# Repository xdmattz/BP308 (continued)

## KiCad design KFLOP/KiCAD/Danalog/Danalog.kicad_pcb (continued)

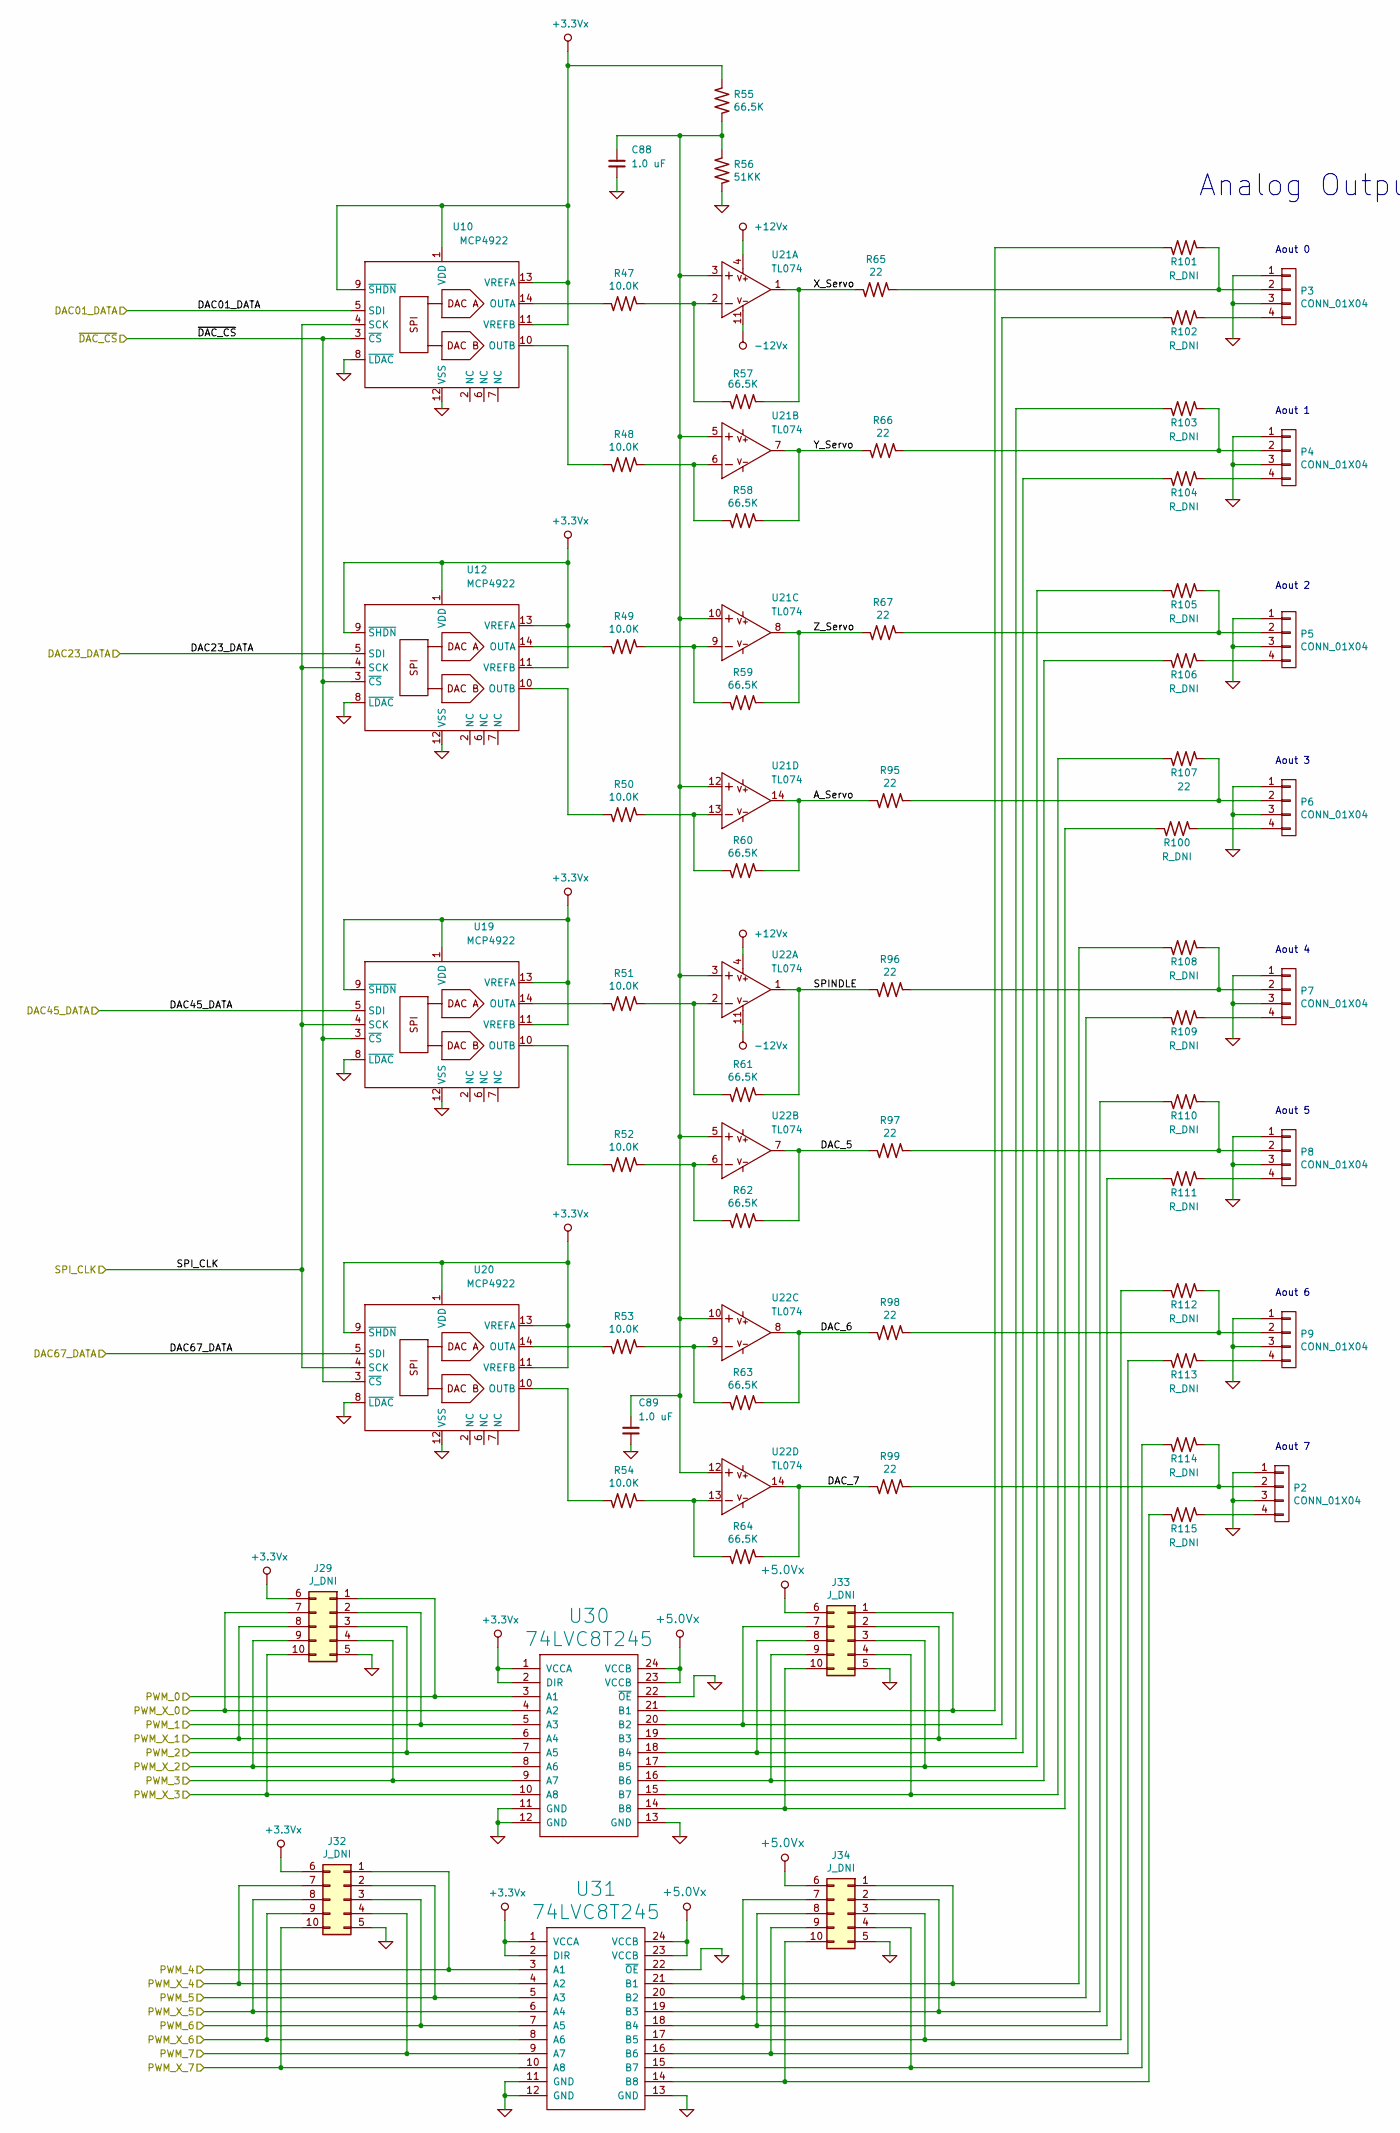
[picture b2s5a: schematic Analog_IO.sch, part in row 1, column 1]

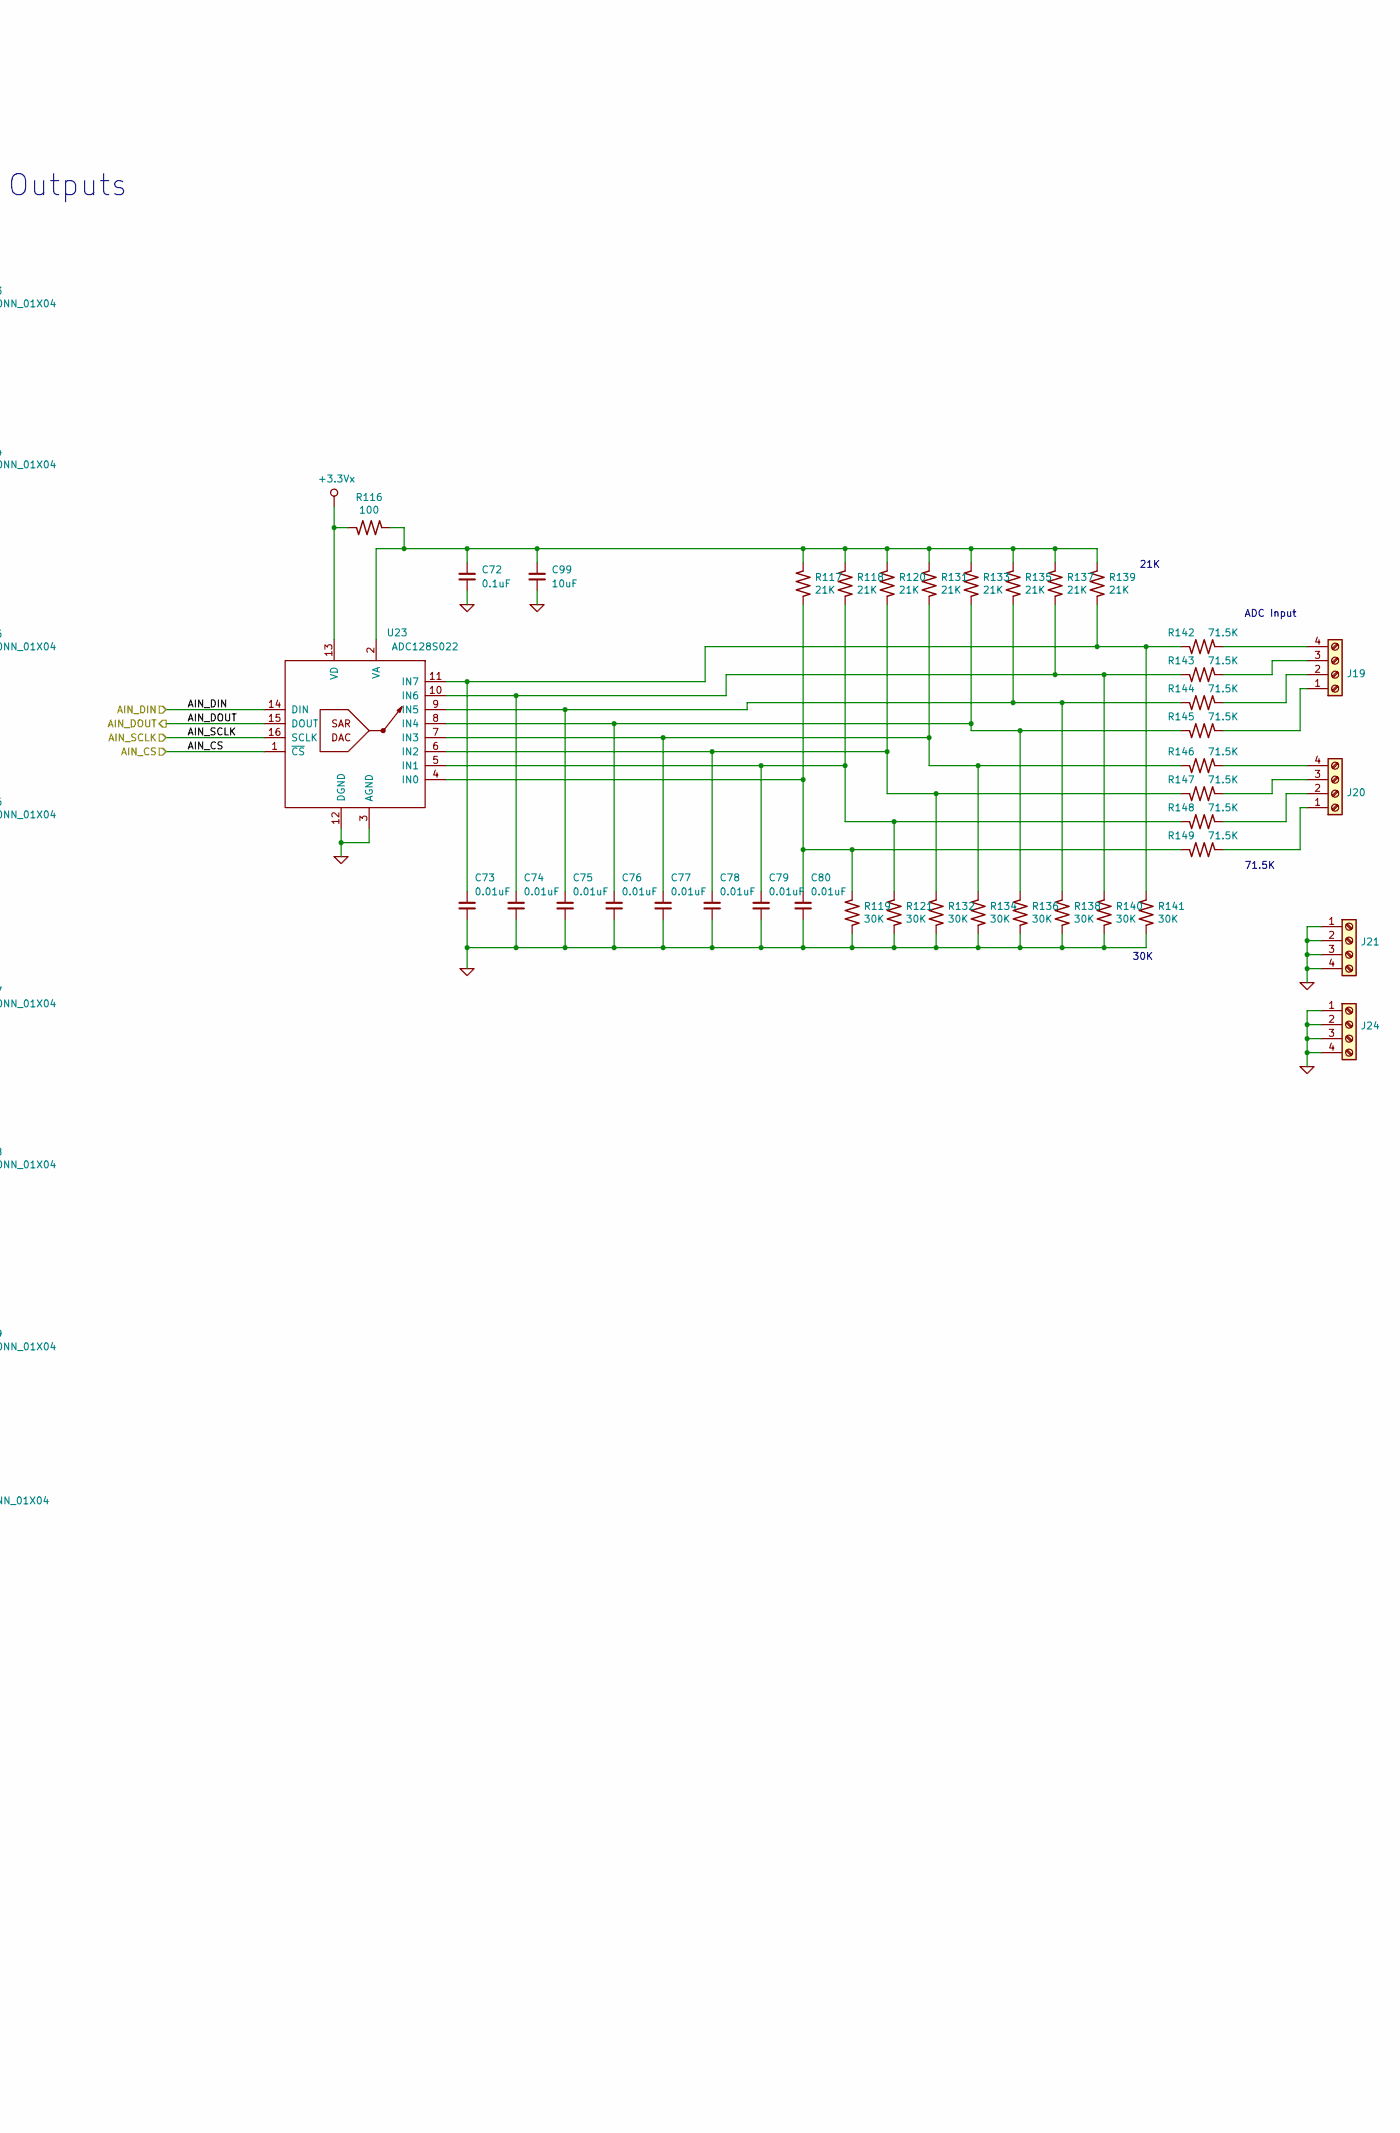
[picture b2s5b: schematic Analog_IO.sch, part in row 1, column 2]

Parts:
C72: 0.1uF; cap_0603
C73, C74, C75, C76, C77, C78, C79, C80: 0.01uF; cap_0603
C88, C89: 1.0 uF; cap_0603
C99: 10uF; cap_0805
J19, J20, J21, J24: Screw_Terminal_01x04; Terminal_Block_RA_4_5_08mm
J29, J32, J33, J34: J_DNI; c-5-103168-3
P2, P3, P4, P5, P6, P7, P8, P9: CONN_01X04; c-5-102202-1
R47, R48, R49, R50, R51, R52, R53, R54: 10.0K; res_0603
R55, R57, R58, R59, R60, R61, R62, R63, R64: 66.5K; res_0603
R56: 51KK; res_0603
R65, R66, R67, R95, R96, R97, R98, R99, R107: 22; res_0603
R100, R101, R102, R103, R104, R105, R106, R108, R109, R110, R111, R112, R113, R114, R115: R_DNI; res_0603
R116: 100; res_0603
R117, R118, R120, R131, R133, R135, R137, R139: 21K; res_0603
R119, R121, R132, R134, R136, R138, R140, R141: 30K; res_0603
R142, R143, R144, R145, R146, R147, R148, R149: 71.5K; res_0603
U10, U12, U19, U20: MCP4922; TSSOP-14_4.4x5mm_Pitch0.65mm
U21, U22: TL074; TSSOP-14_4.4x5mm_Pitch0.65mm
U23: ADC128S022; TSSOP-16
U30, U31: 74LVC8T245; SSOP-24_5.3x8.2mm_Pitch0.65mm

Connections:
+3.3Vx: J29.6, J32.6, R55.2, R116.2, U10.1 (VDD), U10.9 (~SHDN), U10.11 (VREFB), U10.13 (VREFA), U12.1 (VDD), U12.9 (~SHDN), U12.11 (VREFB), U12.13 (VREFA), U19.1 (VDD), U19.9 (~SHDN), U19.11 (VREFB), U19.13 (VREFA), U20.1 (VDD), U20.9 (~SHDN), U20.11 (VREFB), U20.13 (VREFA), U23.13 (VD), U30.1 (VCCA), U30.2 (DIR), U31.1 (VCCA), U31.2 (DIR); also elsewhere on the board
+5.0Vx: J33.6, J34.6, U30.23 (VCCB), U30.24 (VCCB), U31.23 (VCCB), U31.24 (VCCB); also elsewhere on the board
+12Vx: U21.4 (VCC), U22.4 (VCC); also elsewhere on the board
-12Vx: U21.11 (VCC-), U22.11 (VCC-); also elsewhere on the board
/AIN_CS: U23.1 (~CS); also elsewhere on the board
/AIN_DIN: U23.14 (DIN); also elsewhere on the board
/AIN_DOUT: U23.15 (DOUT); also elsewhere on the board
/AIN_SCLK: U23.16 (SCLK); also elsewhere on the board
/Analog/A_Servo: R60.1, R95.2, U21.14 (OUT)
/Analog/DAC_5: R62.1, R97.2, U22.7 (OUT)
/Analog/DAC_6: R63.1, R98.2, U22.8 (OUT)
/Analog/DAC_7: R64.1, R99.2, U22.14 (OUT)
/Analog/SPINDLE: R61.1, R96.2, U22.1 (OUT)
/Analog/X_Servo: R57.1, R65.2, U21.1 (OUT)
/Analog/Y_Servo: R58.1, R66.2, U21.7 (OUT)
/Analog/Z_Servo: R59.1, R67.2, U21.8 (OUT)
/DAC_01: U10.5 (SDI); also elsewhere on the board
/DAC_23: U12.5 (SDI); also elsewhere on the board
/DAC_45: U19.5 (SDI); also elsewhere on the board
/DAC_67: U20.5 (SDI); also elsewhere on the board
/PWM_0: J29.1, U30.3 (A1); also elsewhere on the board
/PWM_1: J29.2, U30.5 (A3); also elsewhere on the board
/PWM_2: J29.3, U30.7 (A5); also elsewhere on the board
/PWM_3: J29.4, U30.9 (A7); also elsewhere on the board
/PWM_4: J32.1, U31.3 (A1); also elsewhere on the board
/PWM_5: J32.2, U31.5 (A3); also elsewhere on the board
/PWM_6: J32.3, U31.7 (A5); also elsewhere on the board
/PWM_7: J32.4, U31.9 (A7); also elsewhere on the board
/PWM_X_0: J29.7, U30.4 (A2); also elsewhere on the board
/PWM_X_1: J29.8, U30.6 (A4); also elsewhere on the board
/PWM_X_2: J29.9, U30.8 (A6); also elsewhere on the board
/PWM_X_3: J29.10, U30.10 (A8); also elsewhere on the board
/PWM_X_4: J32.7, U31.4 (A2); also elsewhere on the board
/PWM_X_5: J32.8, U31.6 (A4); also elsewhere on the board
/PWM_X_6: J32.9, U31.8 (A6); also elsewhere on the board
/PWM_X_7: J32.10, U31.10 (A8); also elsewhere on the board
/SPI_CLK: U10.4 (SCK), U12.4 (SCK), U19.4 (SCK), U20.4 (SCK); also elsewhere on the board
/~DAC_CS: U10.3 (~CS), U12.3 (~CS), U19.3 (~CS), U20.3 (~CS); also elsewhere on the board
GND: C72.2, C73.2, C74.2, C75.2, C76.2, C77.2, C78.2, C79.2, C80.2, C88.2, C89.2, C99.2, J21.1, J21.2, J21.3, J21.4, J24.1, J24.2, J24.3, J24.4, J29.5, J32.5, J33.5, J34.5, P2.1, P2.3, P3.1, P3.3, P4.1, P4.3, P5.1, P5.3, P6.1, P6.3, P7.1, P7.3, P8.1, P8.3, P9.1, P9.3, R56.1, R119.1, R121.1, R132.1, R134.1, R136.1, R138.1, R140.1, R141.1, U10.8 (~LDAC), U10.12 (VSS), U12.8 (~LDAC), U12.12 (VSS), U19.8 (~LDAC), U19.12 (VSS), U20.8 (~LDAC), U20.12 (VSS), U23.3 (AGND), U23.12 (DGND), U30.11 (GND), U30.12 (GND), U30.13 (GND), U30.22 (~OE), U31.11 (GND), U31.12 (GND), U31.13 (GND), U31.22 (~OE); also elsewhere on the board
unnamed: C72.1, C99.1, R116.1, R117.2, R118.2, R120.2, R131.2, R133.2, R135.2, R137.2, R139.2, U23.2 (VA)
unnamed: C73.1, R139.1, R141.2, R142.1, U23.11 (IN7)
unnamed: C74.1, R137.1, R140.2, R143.1, U23.10 (IN6)
unnamed: C75.1, R135.1, R138.2, R144.1, U23.9 (IN5)
unnamed: C76.1, R133.1, R136.2, R145.1, U23.8 (IN4)
unnamed: C77.1, R131.1, R134.2, R146.1, U23.7 (IN3)
unnamed: C78.1, R120.1, R132.2, R147.1, U23.6 (IN2)
unnamed: C79.1, R118.1, R121.2, R148.1, U23.5 (IN1)
unnamed: C80.1, R117.1, R119.2, R149.1, U23.4 (IN0)
unnamed: C88.1, C89.1, R55.1, R56.2, U21.3 (IN+), U21.5 (IN+), U21.10 (IN+), U21.12 (IN+), U22.3 (IN+), U22.5 (IN+), U22.10 (IN+), U22.12 (IN+)
unnamed: J19.1, R145.2
unnamed: J19.2, R144.2
unnamed: J19.3, R143.2
unnamed: J19.4, R142.2
unnamed: J20.1, R149.2
unnamed: J20.2, R148.2
unnamed: J20.3, R147.2
unnamed: J20.4, R146.2
unnamed: J33.1, R101.2, U30.21 (B1)
unnamed: J33.2, R103.2, U30.19 (B3)
unnamed: J33.3, R105.2, U30.17 (B5)
unnamed: J33.4, R107.2, U30.15 (B7)
unnamed: J33.7, R102.2, U30.20 (B2)
unnamed: J33.8, R104.2, U30.18 (B4)
unnamed: J33.9, R106.2, U30.16 (B6)
unnamed: J33.10, R100.2, U30.14 (B8)
unnamed: J34.1, R108.2, U31.21 (B1)
unnamed: J34.2, R110.2, U31.19 (B3)
unnamed: J34.3, R112.2, U31.17 (B5)
unnamed: J34.4, R114.2, U31.15 (B7)
unnamed: J34.7, R109.2, U31.20 (B2)
unnamed: J34.8, R111.2, U31.18 (B4)
unnamed: J34.9, R113.2, U31.16 (B6)
unnamed: J34.10, R115.2, U31.14 (B8)
unnamed: P2.2, R99.1, R114.1
unnamed: P2.4, R115.1
unnamed: P3.2, R65.1, R101.1
unnamed: P3.4, R102.1
unnamed: P4.2, R66.1, R103.1
unnamed: P4.4, R104.1
unnamed: P5.2, R67.1, R105.1
unnamed: P5.4, R106.1
unnamed: P6.2, R95.1, R107.1
unnamed: P6.4, R100.1
unnamed: P7.2, R96.1, R108.1
unnamed: P7.4, R109.1
unnamed: P8.2, R97.1, R110.1
unnamed: P8.4, R111.1
unnamed: P9.2, R98.1, R112.1
unnamed: P9.4, R113.1
unnamed: R47.1, R57.2, U21.2 (IN-)
unnamed: R47.2, U10.14 (OUTA)
unnamed: R48.1, R58.2, U21.6 (IN-)
unnamed: R48.2, U10.10 (OUTB)
unnamed: R49.1, R59.2, U21.9 (IN-)
unnamed: R49.2, U12.14 (OUTA)
unnamed: R50.1, R60.2, U21.13 (IN-)
unnamed: R50.2, U12.10 (OUTB)
unnamed: R51.1, R61.2, U22.2 (IN-)
unnamed: R51.2, U19.14 (OUTA)
unnamed: R52.1, R62.2, U22.6 (IN-)
unnamed: R52.2, U19.10 (OUTB)
unnamed: R53.1, R63.2, U22.9 (IN-)
unnamed: R53.2, U20.14 (OUTA)
unnamed: R54.1, R64.2, U22.13 (IN-)
unnamed: R54.2, U20.10 (OUTB)

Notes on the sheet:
ADC Input
30K
71.5K
21K
Analog Outputs
Aout 0
Aout 1
Aout 2
Aout 3
Aout 4
Aout 5
Aout 6
Aout 7

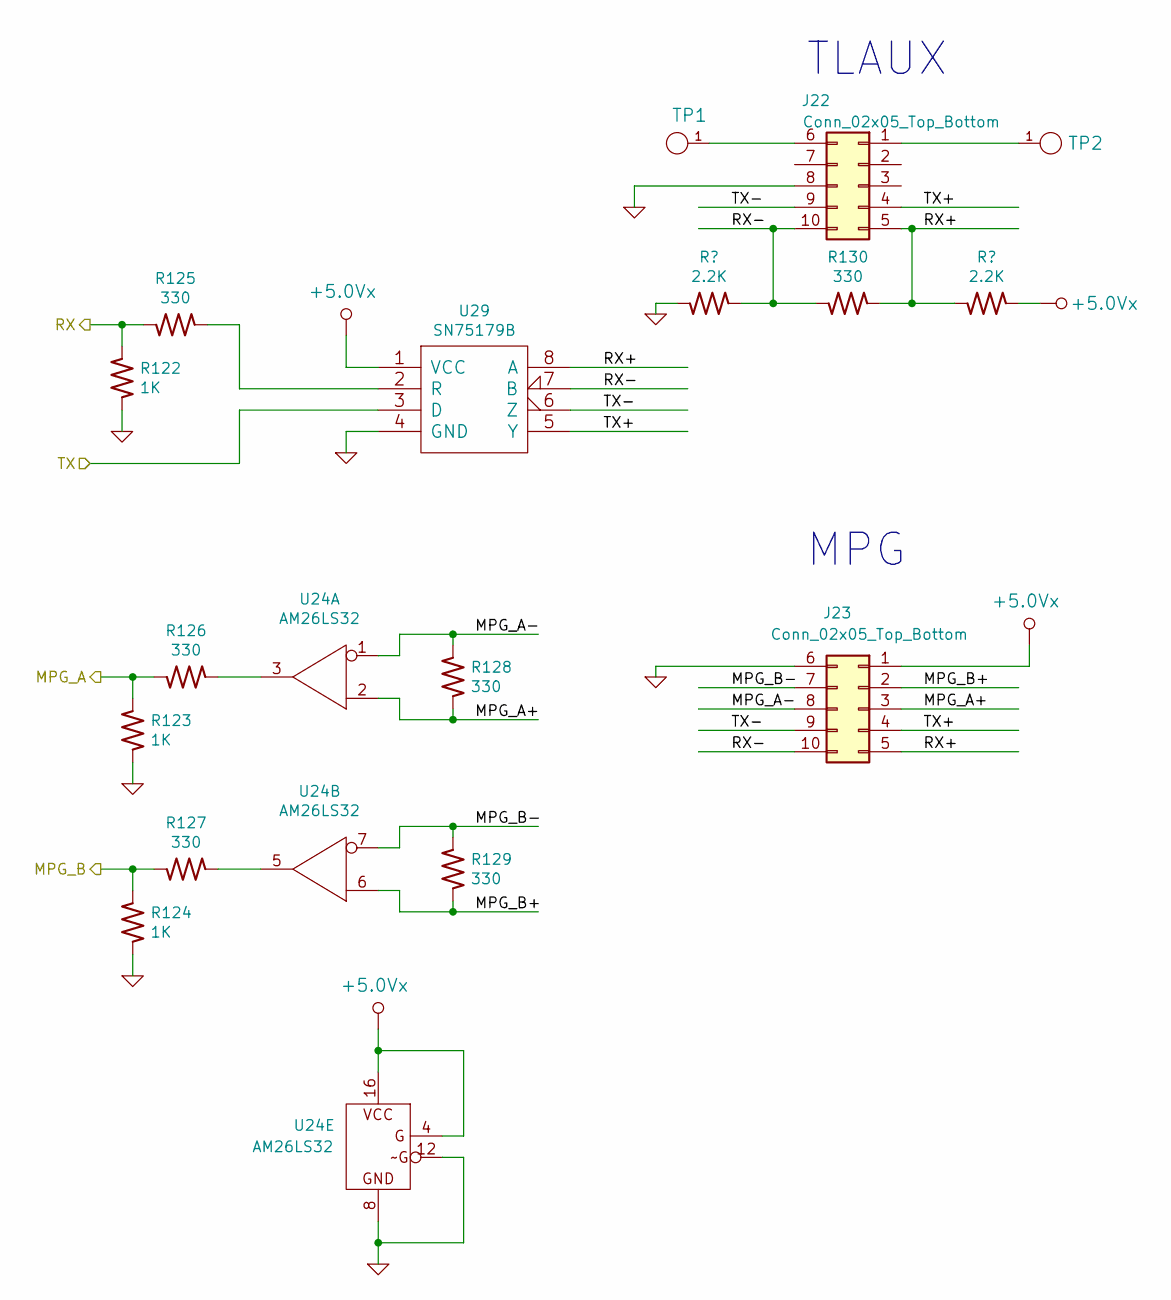
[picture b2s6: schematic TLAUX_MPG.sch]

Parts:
J22, J23: Conn_02x05_Top_Bottom; c-5-103168-3
R122, R123, R124: 1K; res_0603
R125, R126, R127, R128, R129, R130: 330; res_0603
TP1, TP2: TEST_POINT; TP60
U24: AM26LS32; SOIC-16_3.9x9.9mm_Pitch1.27mm
U29: SN75179B; SOIC-8

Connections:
+5.0Vx: J23.1, U24.4 (G), U24.16 (VCC), U29.1 (VCC); also elsewhere on the board
/MPG_A: R123.2, R126.2; also elsewhere on the board
/MPG_B: R124.2, R127.2; also elsewhere on the board
/RS232R_3V: R122.2, R125.2; also elsewhere on the board
/RS232X_3V: U29.3 (D); also elsewhere on the board
/TLAUX_MPG/MPG_A+: J23.3, R128.1, U24.2 (1A)
/TLAUX_MPG/MPG_A-: J23.8, R128.2, U24.1 (1B)
/TLAUX_MPG/MPG_B+: J23.2, R129.1, U24.6 (2A)
/TLAUX_MPG/MPG_B-: J23.7, R129.2, U24.7 (2B)
/TLAUX_MPG/RX+: J22.5, J23.5, R130.1, U29.8 (A)
/TLAUX_MPG/RX-: J22.10, J23.10, R130.2, U29.7 (B)
/TLAUX_MPG/TX+: J22.4, J23.4, U29.5 (Y)
/TLAUX_MPG/TX-: J22.9, J23.9, U29.6 (Z)
GND: J22.8, J23.6, R122.1, R123.1, R124.1, U24.8 (GND), U24.12 (~G), U29.4 (GND); also elsewhere on the board
unnamed: J22.1, TP2.1
unnamed: J22.6, TP1.1
unnamed: R125.1, U29.2 (R)
unnamed: R126.1, U24.3 (1Y)
unnamed: R127.1, U24.5 (2Y)

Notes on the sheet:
MPG
TLAUX

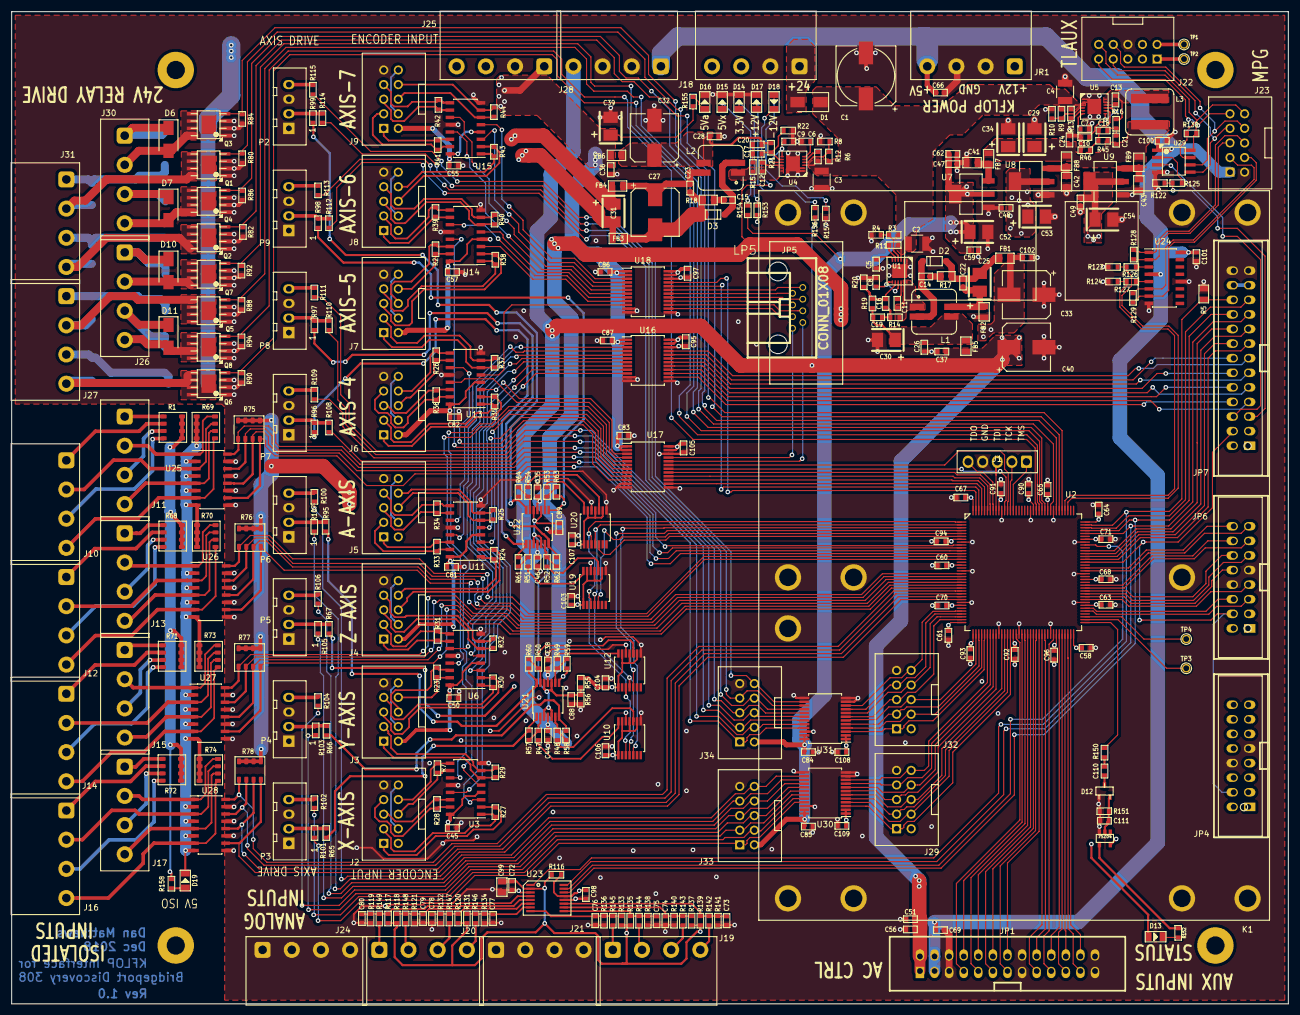
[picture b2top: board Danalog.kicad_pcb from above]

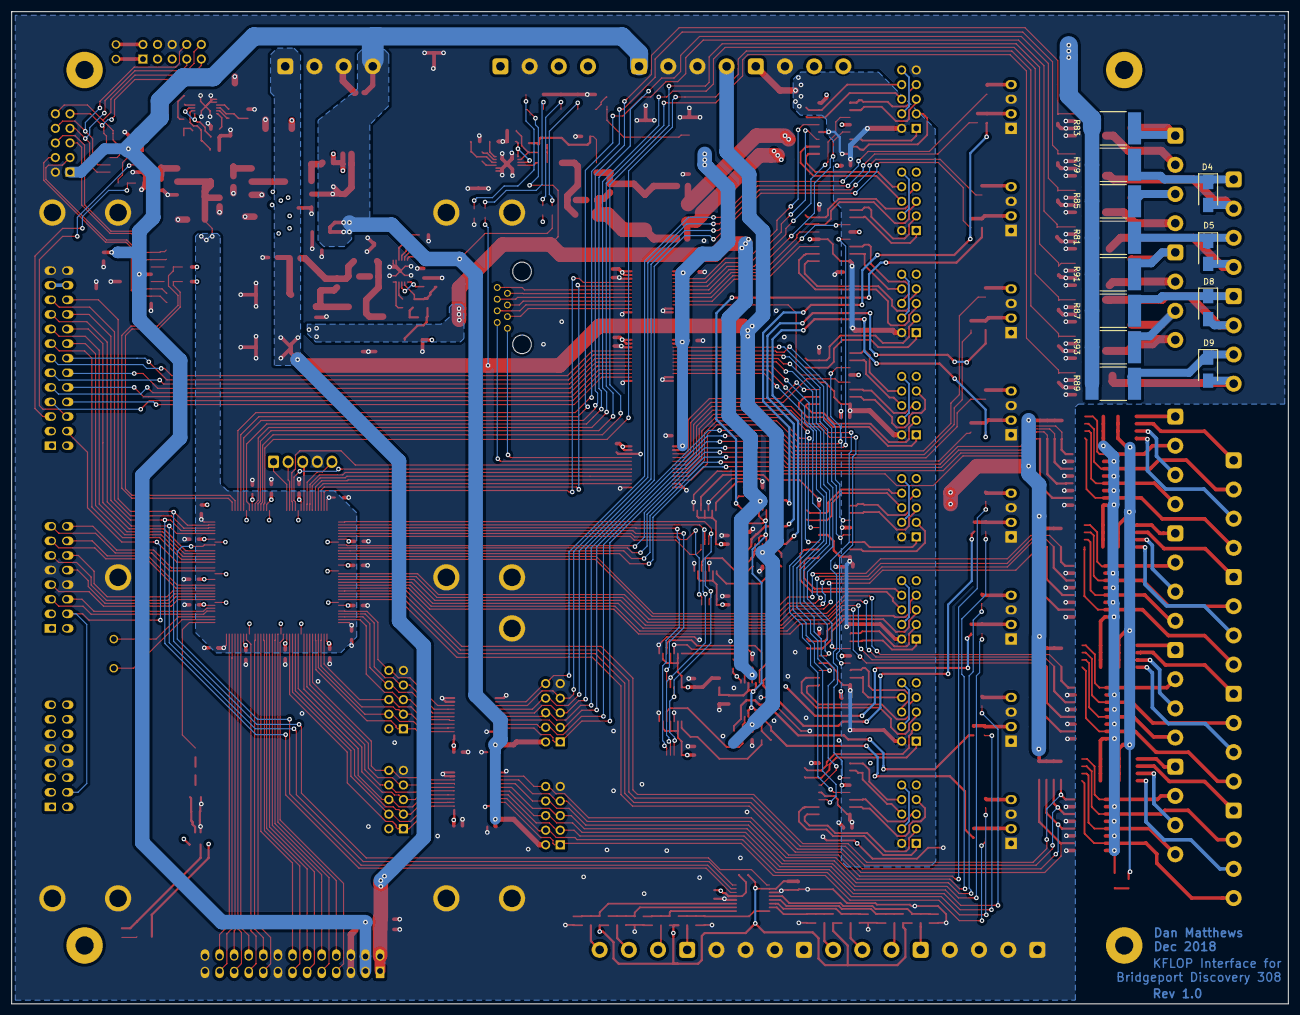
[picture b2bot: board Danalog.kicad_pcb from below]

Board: 4 copper layers, 222.2 x 172.7 mm, 393 parts (12 on the bottom side), 393 nets.

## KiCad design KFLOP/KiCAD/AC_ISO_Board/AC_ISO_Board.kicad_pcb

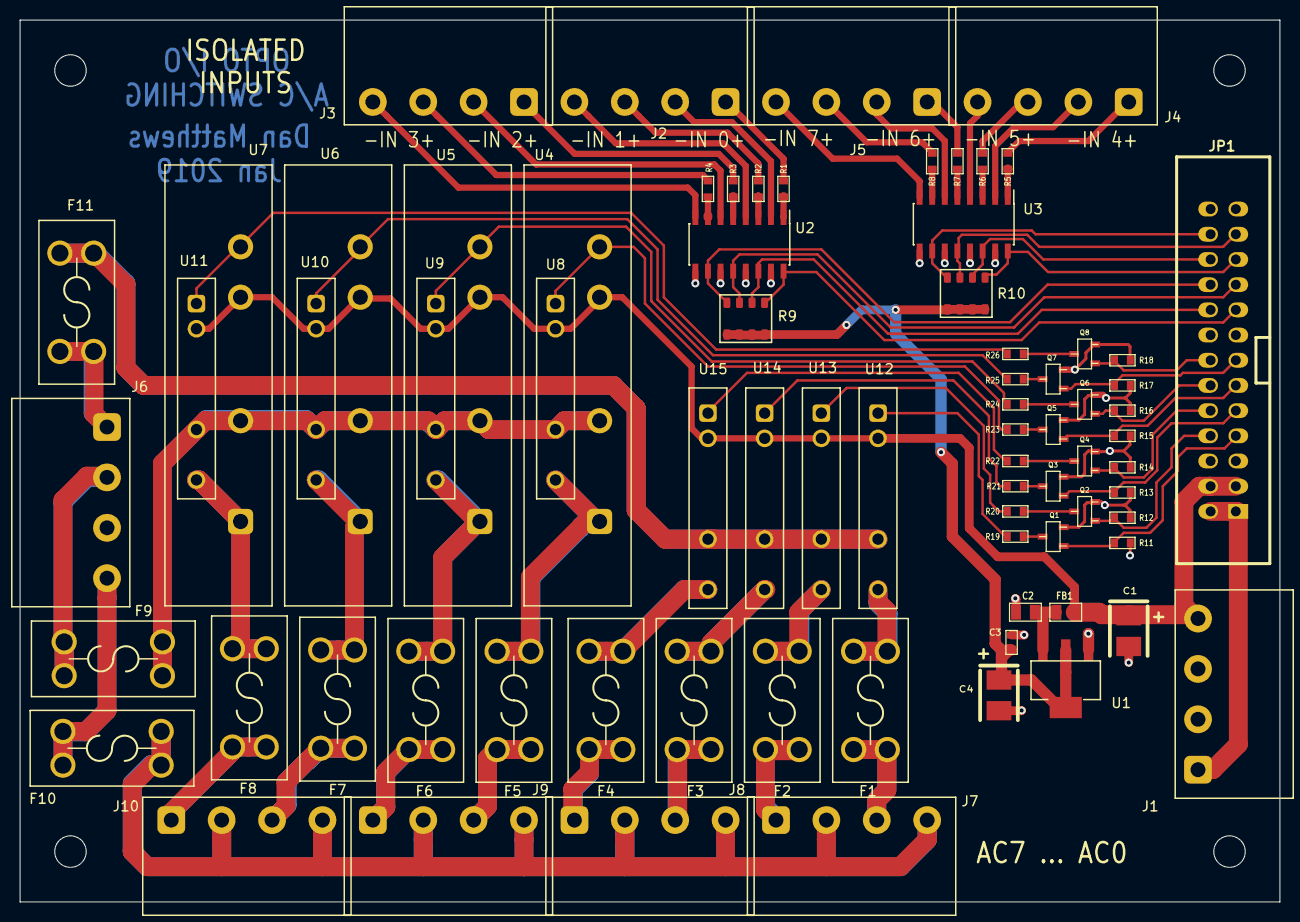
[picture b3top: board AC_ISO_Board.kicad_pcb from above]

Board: 2 copper layers, 127.0 x 88.9 mm, 76 parts (0 on the bottom side), 83 nets.

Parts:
C1, C4: 100uF 6.3V; Tan_Cap_B
C2: 10uF; cap_0805
C3: 0.1uF; cap_0603
F1, F2, F3, F4, F5, F6, F7, F8, F9, F10, F11: Fuse; FUSE_Holder_297
FB1: FB_60 Ohm; fb_0805
J1, J2, J3, J4, J5, J6, J7, J8, J9, J10: Screw_Terminal_01x04; Terminal_Block_RA_4_5_08mm
JP1: CONN_02X13; vasch_strip_13x2
Q1, Q2, Q3, Q4, Q5, Q6, Q7, Q8: BSS-123; sot-23
R1, R2, R3, R4, R5, R6, R7, R8, R19, R20, R21, R22, R23, R24, R25, R26: 2.2K; res_0603
R9, R10: 2.2K; RES_ARRAY_2012
R11, R12, R13, R14, R15, R16, R17, R18: 10K; res_0603
U1: TLV1117LV33; SOT-223
U2, U3: TLP291-4; SOIC-16_3.9x9.9mm_Pitch1.27mm
U4, U5, U6, U7: OACM-UJ
U8, U9, U10, U11, U12, U13, U14, U15: CPC1966; CPC1966Y

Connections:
+3.3Vx: C3.2, C4.1, R9.1, R9.2, R9.3, R9.4, R10.1, R10.2, R10.3, R10.4, U1.2, U1.4
+5.0Vx: C1.1, FB1.2, J1.4, JP1.3, JP1.4, U4.3, U5.3, U6.3, U7.3, U8.2, U9.2, U10.2, U11.2, U12.2, U13.2, U14.2, U15.2
+12Vx: J1.1, JP1.1, JP1.2
/AC_0: JP1.7, Q1.1, R11.2
/AC_1: JP1.8, Q2.1, R12.2
/AC_2: JP1.9, Q3.1, R13.2
/AC_3: JP1.10, Q4.1, R14.2
/AC_4: JP1.11, Q5.1, R15.2
/AC_5: JP1.12, Q6.1, R16.2
/AC_6: JP1.13, Q7.1, R17.2
/AC_7: JP1.14, Q8.1, R18.2
/AUX_IN_0: JP1.17, R9.5, U2.16
/AUX_IN_1: JP1.18, R9.6, U2.14
/AUX_IN_2: JP1.19, R9.7, U2.12
/AUX_IN_3: JP1.20, R9.8, U2.10
/AUX_IN_4: JP1.21, R10.5, U3.16
/AUX_IN_5: JP1.22, R10.6, U3.14
/AUX_IN_6: JP1.23, R10.7, U3.12
/AUX_IN_7: JP1.24, R10.8, U3.10
GND: C1.2, C2.1, C3.1, C4.2, J1.2, J1.3, JP1.5, JP1.6, JP1.15, JP1.16, JP1.25, JP1.26, Q1.2, Q2.2, Q3.2, Q4.2, Q5.2, Q6.2, Q7.2, Q8.2, R11.1, R12.1, R13.1, R14.1, R15.1, R16.1, R17.1, R18.1, U1.1, U2.9, U2.11, U2.13, U2.15, U3.9, U3.11, U3.13, U3.15
unnamed: C2.2, FB1.1, U1.3
unnamed: F1.1, J7.3
unnamed: F1.2, U12.4
unnamed: F2.1, J7.1
unnamed: F2.2, U13.4
unnamed: F3.1, J8.3
unnamed: F3.2, U14.4
unnamed: F4.1, J8.1
unnamed: F4.2, U15.4
unnamed: F5.1, J9.3
unnamed: F5.2, U4.1, U8.4
unnamed: F6.1, J9.1
unnamed: F6.2, U5.1, U9.4
unnamed: F7.1, J10.3
unnamed: F7.2, U6.1, U10.4
unnamed: F8.1, J10.1
unnamed: F8.2, U7.1, U11.4
unnamed: F9.1, J6.2
unnamed: F9.2, U4.2, U5.2, U6.2, U7.2, U8.3, U9.3, U10.3, U11.3
unnamed: F10.1, J6.4
unnamed: F10.2, J7.2, J7.4, J8.2, J8.4, J9.2, J9.4, J10.2, J10.4
unnamed: F11.1, J6.1
unnamed: F11.2, U12.3, U13.3, U14.3, U15.3
unnamed: J2.1, R1.2
unnamed: J2.2, U2.2
unnamed: J2.3, R2.2
unnamed: J2.4, U2.4
unnamed: J3.1, R3.2
unnamed: J3.2, U2.6
unnamed: J3.3, R4.2
unnamed: J3.4, U2.8
unnamed: J4.1, R5.2
unnamed: J4.2, U3.2
unnamed: J4.3, R6.2
unnamed: J4.4, U3.4
unnamed: J5.1, R7.2
unnamed: J5.2, U3.6
unnamed: J5.3, R8.2
unnamed: J5.4, U3.8
unnamed: Q1.3, R19.2
unnamed: Q2.3, R20.2
unnamed: Q3.3, R21.2
unnamed: Q4.3, R22.2
unnamed: Q5.3, R23.2
unnamed: Q6.3, R24.2
unnamed: Q7.3, R25.2
unnamed: Q8.3, R26.2
unnamed: R1.1, U2.1
unnamed: R2.1, U2.3
unnamed: R3.1, U2.5
unnamed: R4.1, U2.7
unnamed: R5.1, U3.1
unnamed: R6.1, U3.3
unnamed: R7.1, U3.5
unnamed: R8.1, U3.7
unnamed: R19.1, U12.1
unnamed: R20.1, U13.1
unnamed: R21.1, U14.1
unnamed: R22.1, U15.1
unnamed: R23.1, U4.4, U8.1
unnamed: R24.1, U5.4, U9.1
unnamed: R25.1, U6.4, U10.1
unnamed: R26.1, U7.4, U11.1

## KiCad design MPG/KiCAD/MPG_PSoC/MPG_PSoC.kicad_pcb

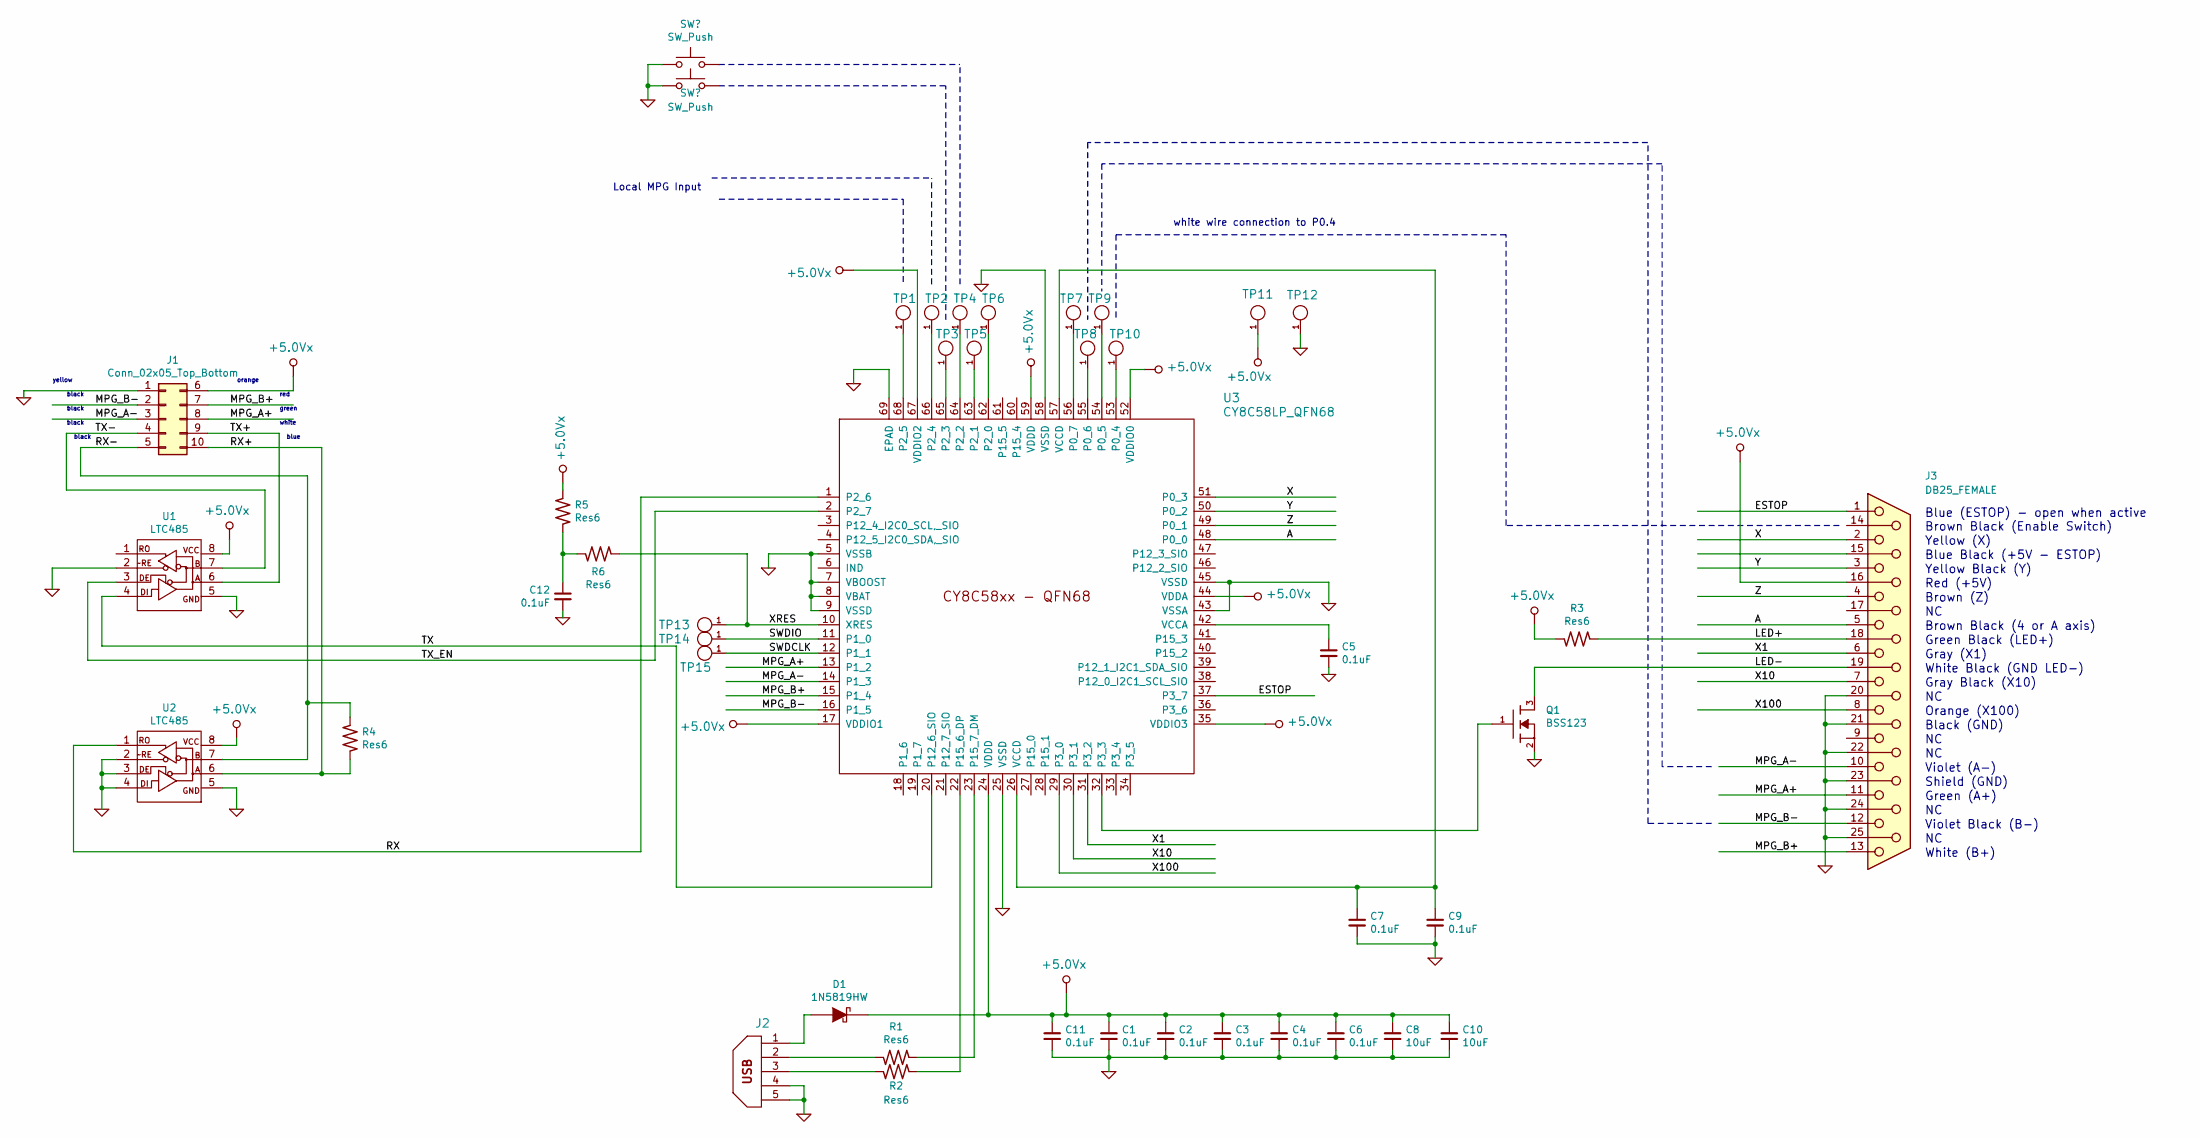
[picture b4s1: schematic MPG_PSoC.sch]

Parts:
C1, C2, C3, C4, C5, C6, C7, C9, C11, C12: 0.1uF; cap_0603
C8, C10: 10uF; cap_1210
D1: 1N5819HW; SOD-123
J1: Conn_02x05_Top_Bottom; c-5-103168-3
J2: USB_micro-B; conn_usb_B_mini_smd
J3: DB25_FEMALE; DB25_F_Edge
Q1: BSS123; sot-23
R1, R2, R3, R4, R5, R6: Res6; res_0603
TP1, TP2, TP3, TP4, TP5, TP6, TP7, TP8, TP9, TP10, TP11, TP12, TP13, TP14, TP15: TP; TP60
U1, U2: LTC485; SOIC-8
U3: CY8C58LP_QFN68; QFN_68

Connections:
+5.0Vx: C1.1, C2.1, C3.1, C4.1, C6.1, C8.1, C10.1, C11.1, D1.2 (K), J1.6, J3.16, R3.2, R5.2, TP11.1, U1.8 (VCC), U2.8 (VCC), U3.17 (VDDIO1), U3.24 (VDDD), U3.35 (VDDIO3), U3.44 (VDDA), U3.52 (VDDIO0), U3.59 (VDDD), U3.67 (VDDIO2)
/A: J3.5, U3.48 (P0_0)
/ESTOP: J3.1, U3.37 (P3_7)
/LED+: J3.18, R3.1
/LED-: J3.19, Q1.3 (D)
/MPG_A+: J1.8, J3.11, U3.13 (P1_2)
/MPG_A-: J1.3, J3.10, U3.14 (P1_3)
/MPG_B+: J1.7, J3.13, U3.15 (P1_4)
/MPG_B-: J1.2, J3.12, U3.16 (P1_5)
/RX: U2.1 (RO), U3.1 (P2_6)
/RX+: J1.10, R4.1, U2.6 (A)
/RX-: J1.5, R4.2, U2.7 (B)
/SWDCLK: TP15.1, U3.12 (P1_1)
/SWDIO: TP14.1, U3.11 (P1_0)
/TX: U1.3 (DE), U3.2 (P2_7)
/TX+: J1.9, U1.6 (A)
/TX-: J1.4, U1.7 (B)
/TX_EN: U1.4 (DI), U3.20 (P12_6_SIO)
/X: J3.2, U3.51 (P0_3)
/X1: J3.6, U3.31 (P3_2)
/X10: J3.7, U3.30 (P3_1)
/X100: J3.8, U3.29 (P3_0)
/XRES: R6.2, TP13.1, U3.10 (XRES)
/Y: J3.3, U3.50 (P0_2)
/Z: J3.4, U3.49 (P0_1)
GND: C1.2, C2.2, C3.2, C4.2, C5.2, C6.2, C7.2, C8.2, C9.2, C10.2, C11.2, C12.2, J1.1, J2.4, J2.5, J3.20, J3.21, J3.22, J3.23, J3.24, J3.25, Q1.2 (S), TP12.1, U1.2 (~RE), U1.5 (GND), U2.2 (~RE), U2.3 (DE), U2.4 (DI), U2.5 (GND), U3.5 (VSSB), U3.7 (VBOOST), U3.8 (VBAT), U3.9 (VSSD), U3.25 (VSSD), U3.43 (VSSA), U3.45 (VSSD), U3.58 (VSSD), U3.69 (EPAD)
unnamed: C5.1, U3.42 (VCCA)
unnamed: C7.1, C9.1, U3.26 (VCCD), U3.57 (VCCD)
unnamed: C12.1, R5.1, R6.1
unnamed: D1.1 (A), J2.1
unnamed: J2.2, R1.2
unnamed: J2.3, R2.2
unnamed: Q1.1 (G), U3.32 (P3_3)
unnamed: R1.1, U3.23 (P15_7_DM)
unnamed: R2.1, U3.22 (P15_6_DP)
unnamed: TP1.1, U3.68 (P2_5)
unnamed: TP2.1, U3.66 (P2_4)
unnamed: TP3.1, U3.65 (P2_3)
unnamed: TP4.1, U3.64 (P2_2)
unnamed: TP5.1, U3.63 (P2_1)
unnamed: TP6.1, U3.62 (P2_0)
unnamed: TP7.1, U3.56 (P0_7)
unnamed: TP8.1, U3.55 (P0_6)
unnamed: TP9.1, U3.54 (P0_5)
unnamed: TP10.1, U3.53 (P0_4)

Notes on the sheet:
Green Black (LED+)
Gray (X1)
Yellow (X)
Yellow Black (Y)
Brown (Z)
Brown Black (4 or A axis)
White Black (GND LED-)
Gray Black (X10)
Blue (ESTOP) - open when active
Blue Black (+5V - ESTOP)
Red (+5V)
Orange (X100)
Violet Black (B-)
White (B+)
Violet (A-)
Shield (GND)
Green (A+)
Black (GND)
Brown Black (Enable Switch)
yellow
orange
red
black
green
blue
white
white wire connection to P0.4
Local MPG Input
